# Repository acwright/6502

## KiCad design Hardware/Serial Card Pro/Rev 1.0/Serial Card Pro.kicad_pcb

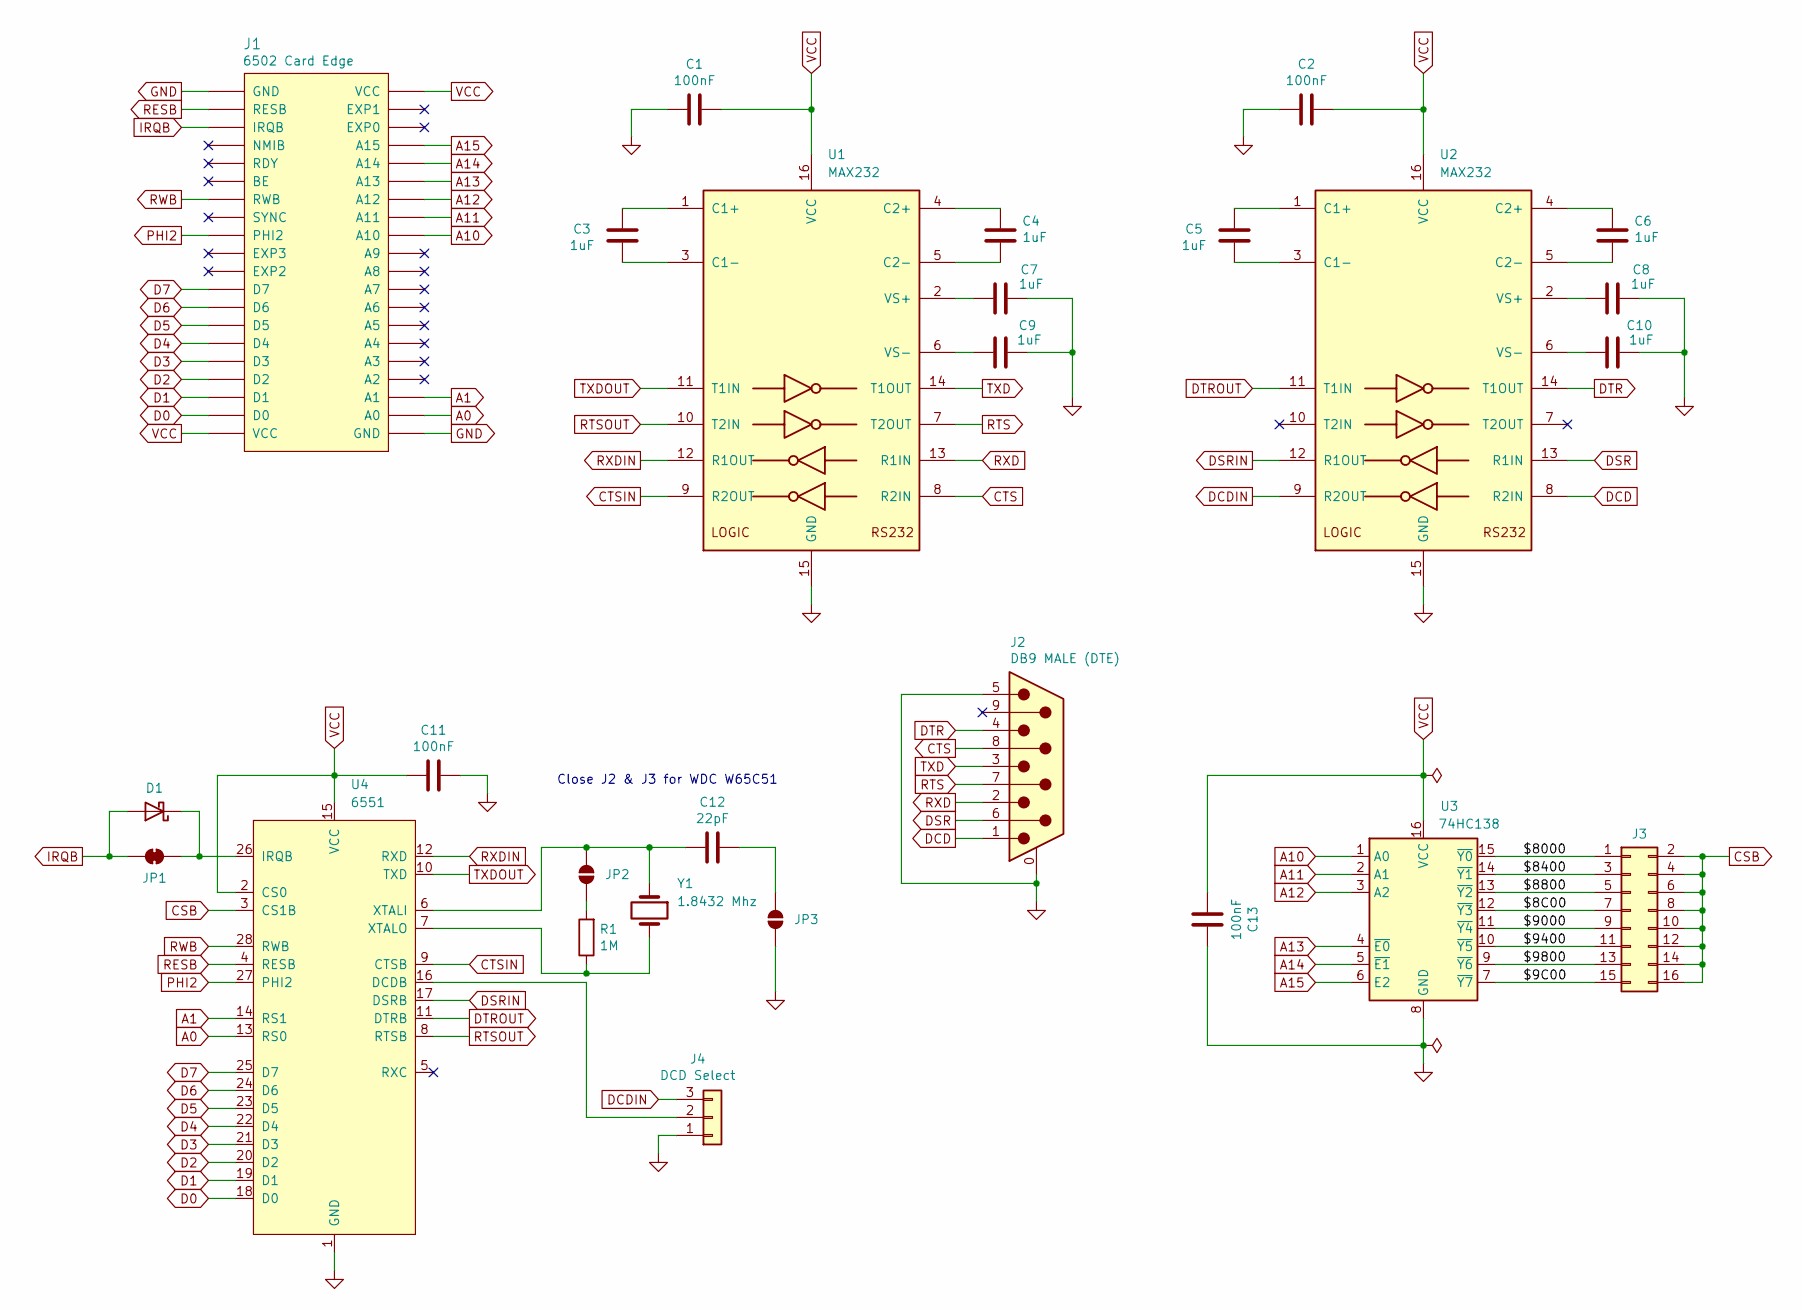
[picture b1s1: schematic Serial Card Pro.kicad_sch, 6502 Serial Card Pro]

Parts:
C1, C2, C11, C13: 100nF; C_0805_2012Metric; LCSC C49678
C3, C4, C5, C6, C7, C8, C9, C10: 1uF; C_0805_2012Metric; LCSC C28323
C12: 22pF; C_0805_2012Metric; LCSC C1804
D1: D_Schottky; D_DO-35_SOD27_P7.62mm_Horizontal
J1: 6502 Card Edge
J2: DB9 MALE (DTE); DSUB-9_Pins_Horizontal_P2.77x2.84mm_EdgePinOffset7.70mm_Hou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; MPN D09P33E4GX00LF; Digikey 609-1481-ND
J3: Conn_02x08_Odd_Even; PinHeader_2x08_P2.54mm_Vertical
J4: DCD Select; PinHeader_1x03_P2.54mm_Vertical
JP1: SolderJumper_2_Bridged; SolderJumper-2_P1.3mm_Bridged_RoundedPad1.0x1.5mm
JP2, JP3: SolderJumper_2_Open; SolderJumper-2_P1.3mm_Open_RoundedPad1.0x1.5mm
R1: 1M; R_0805_2012Metric; LCSC C103906
U1, U2: MAX232; MAX232D; LCSC C59824
U3: 74HC138; SOIC-16_3.9x9.9mm_P1.27mm; LCSC C5602
U4: 6551; DIP-28_W15.24mm_Socket_LongPads
Y1: 1.8432 Mhz; Crystal_HC49-U_Vertical

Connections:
/$8C00: J3.7, U3.12 (~Y3)
/$9C00: J3.15, U3.7 (~Y7)
/$8000: J3.1, U3.15 (~Y0)
/$8400: J3.3, U3.14 (~Y1)
/$8800: J3.5, U3.13 (~Y2)
/$9000: J3.9, U3.11 (~Y4)
/$9400: J3.11, U3.10 (~Y5)
/$9800: J3.13, U3.9 (~Y6)
A0: J1.A0, U4.13 (RS0)
A1: J1.A1, U4.14 (RS1)
A10: J1.A10, U3.1 (A0)
A11: J1.A11, U3.2 (A1)
A12: J1.A12, U3.3 (A2)
A13: J1.A13, U3.4 (~E0)
A14: J1.A14, U3.5 (~E1)
A15: J1.A15, U3.6 (E2)
CSB: J3.2, J3.4, J3.6, J3.8, J3.10, J3.12, J3.14, J3.16, U4.3 (CS1B)
CTS: J2.8, U1.8 (R2IN)
CTSIN: U1.9 (R2OUT), U4.9 (CTSB)
D0: J1.D0, U4.18 (D0)
D1: J1.D1, U4.19 (D1)
D2: J1.D2, U4.20 (D2)
D3: J1.D3, U4.21 (D3)
D4: J1.D4, U4.22 (D4)
D5: J1.D5, U4.23 (D5)
D6: J1.D6, U4.24 (D6)
D7: J1.D7, U4.25 (D7)
DCD: J2.1, U2.8 (R2IN)
DCDIN: J4.3, U2.9 (R2OUT)
DSR: J2.6, U2.13 (R1IN)
DSRIN: U2.12 (R1OUT), U4.17 (DSRB)
DTR: J2.4, U2.14 (T1OUT)
DTROUT: U2.11 (T1IN), U4.11 (DTRB)
GND: C1.1, C2.1, C7.2, C8.2, C9.2, C10.2, C11.2, C13.2, J1.GND, J2.0 (PAD), J2.5, J4.1, JP3.1 (A), U1.15 (GND), U2.15 (GND), U3.8 (GND), U4.1 (GND)
IRQB: D1.2 (A), J1.IRQB, JP1.1 (A)
unnamed: D1.1 (K), JP1.2 (B), U4.26 (IRQB)
unnamed: J4.2, U4.16 (DCDB)
unnamed: JP2.1 (A), R1.2
unnamed: C12.2, JP2.2 (B), U4.6 (XTALI), Y1.1
unnamed: C12.1, JP3.2 (B)
unnamed: C3.1, U1.1 (C1+)
unnamed: C3.2, U1.3 (C1-)
unnamed: C4.1, U1.4 (C2+)
unnamed: C4.2, U1.5 (C2-)
unnamed: C7.1, U1.2 (VS+)
unnamed: C9.1, U1.6 (VS-)
unnamed: C5.1, U2.1 (C1+)
unnamed: C5.2, U2.3 (C1-)
unnamed: C6.1, U2.4 (C2+)
unnamed: C6.2, U2.5 (C2-)
unnamed: C8.1, U2.2 (VS+)
unnamed: C10.1, U2.6 (VS-)
unnamed: R1.1, U4.7 (XTALO), Y1.2
PHI2: J1.PHI2, U4.27 (PHI2)
RESB: J1.RESB, U4.4 (RESB)
RTS: J2.7, U1.7 (T2OUT)
RTSOUT: U1.10 (T2IN), U4.8 (RTSB)
RWB: J1.RWB, U4.28 (RWB)
RXD: J2.2, U1.13 (R1IN)
RXDIN: U1.12 (R1OUT), U4.12 (RXD)
TXD: J2.3, U1.14 (T1OUT)
TXDOUT: U1.11 (T1IN), U4.10 (TXD)
VCC: C1.2, C2.2, C11.1, C13.1, J1.VCC, U1.16 (VCC), U2.16 (VCC), U3.16 (VCC), U4.2 (CS0), U4.15 (VCC)

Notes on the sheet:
Close J2 & J3 for WDC W65C51

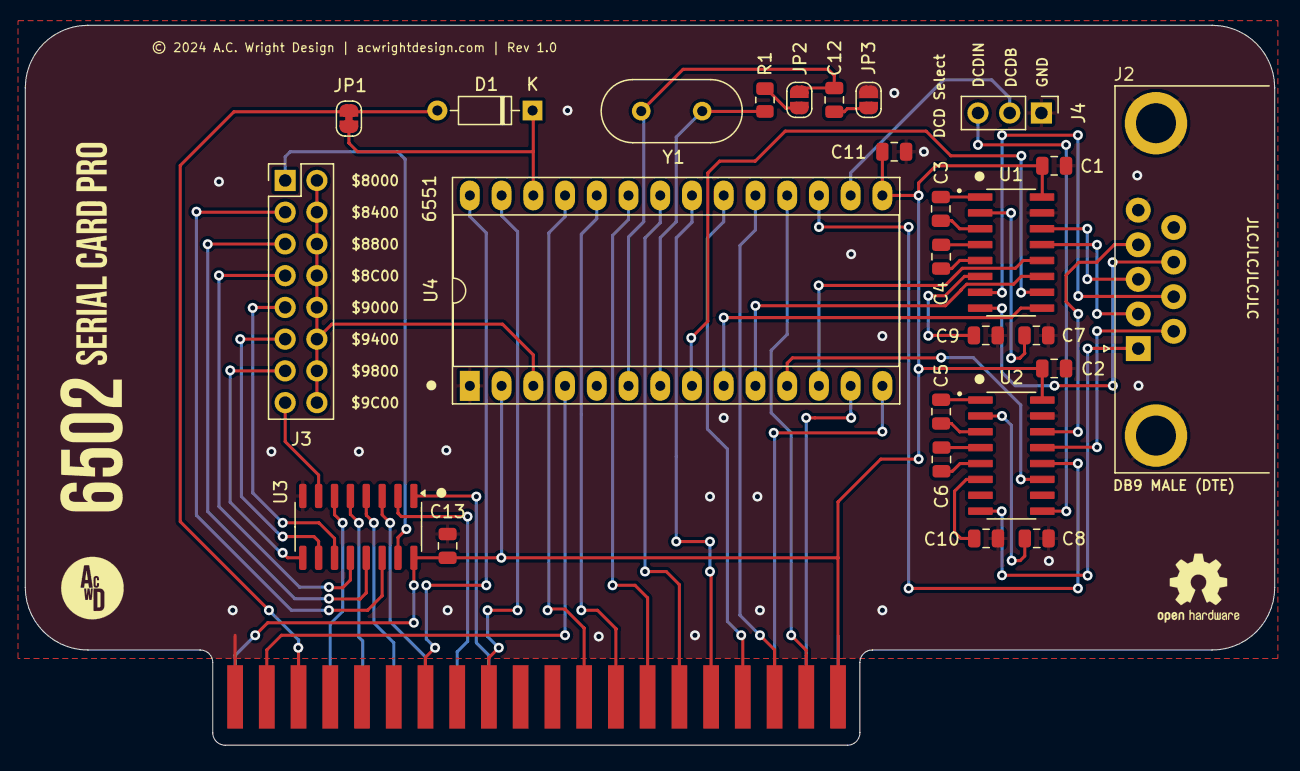
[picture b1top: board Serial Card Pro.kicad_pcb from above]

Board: 2 copper layers, 100.0 x 57.6 mm, 27 parts (0 on the bottom side), 63 nets.

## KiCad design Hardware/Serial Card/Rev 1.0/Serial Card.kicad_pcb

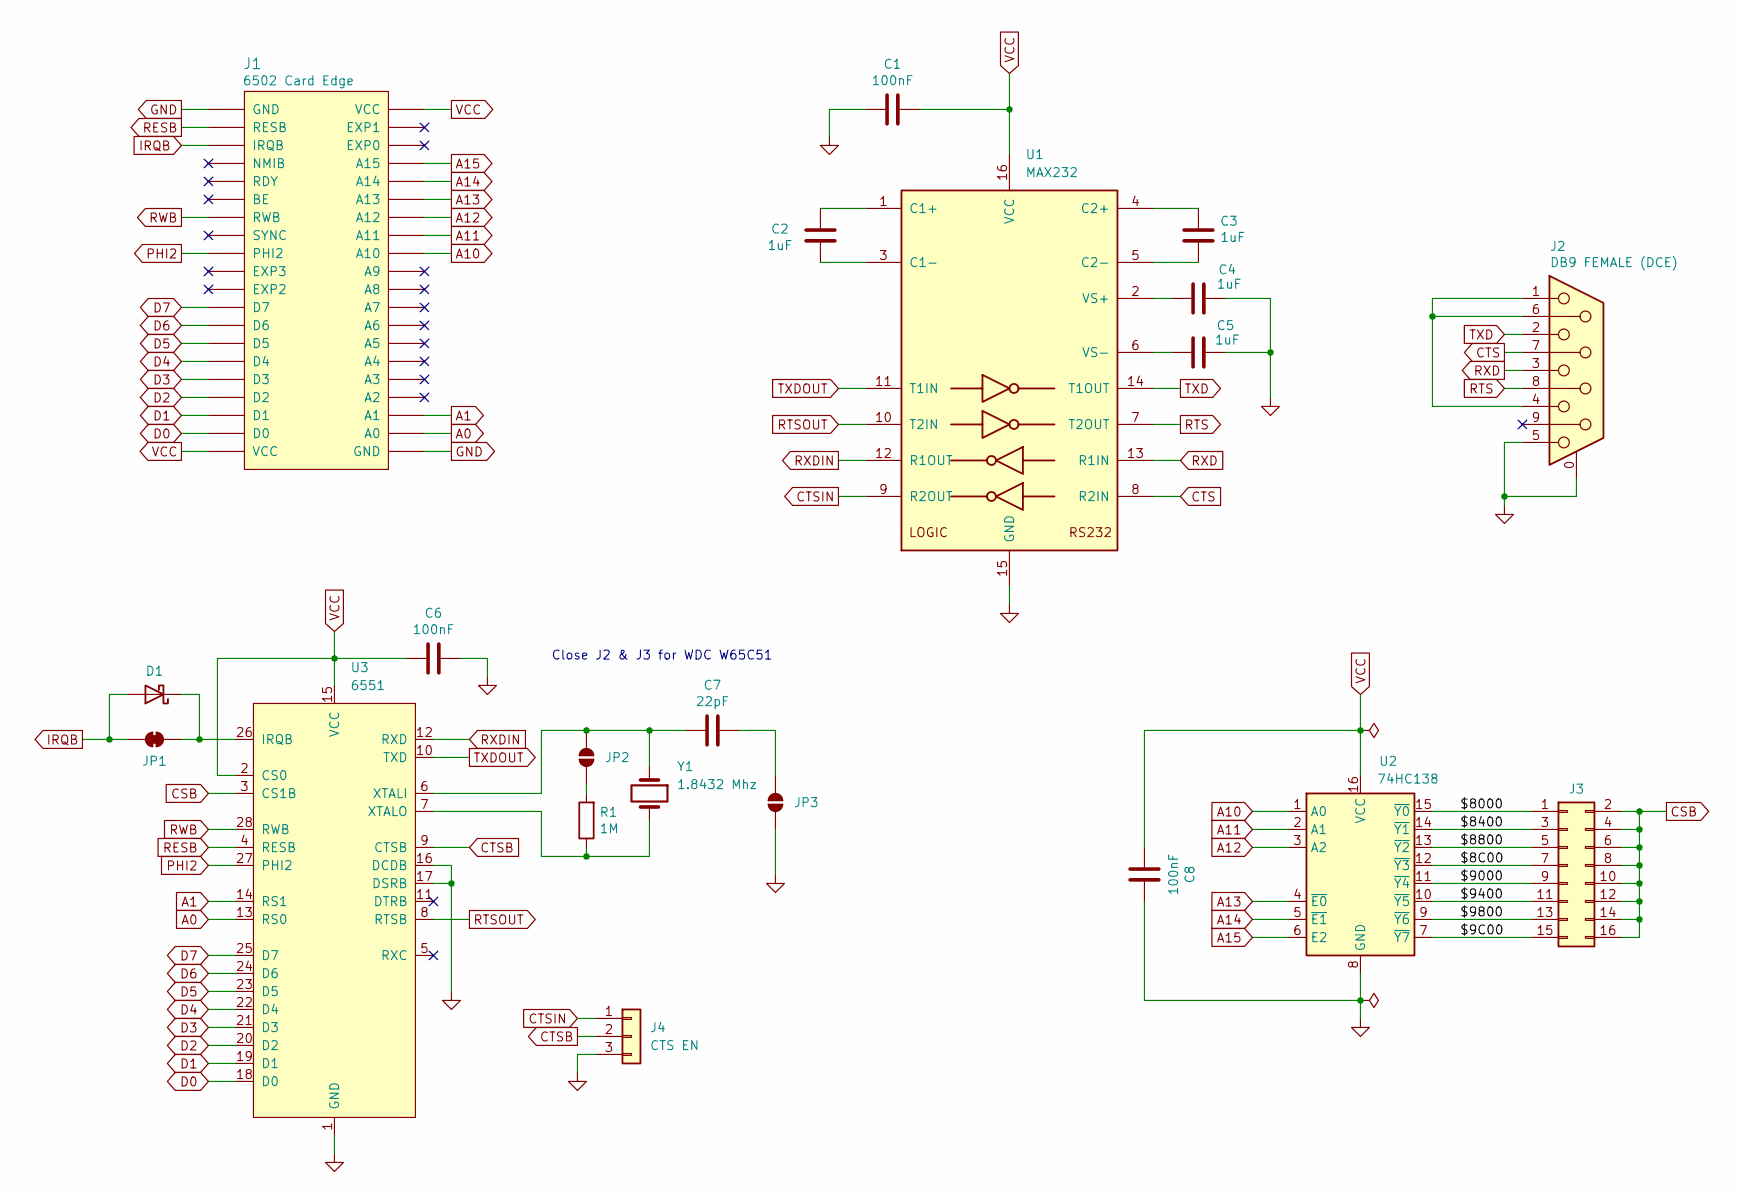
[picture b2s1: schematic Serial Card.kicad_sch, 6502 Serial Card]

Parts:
C1, C6, C8: 100nF; C_0805_2012Metric; LCSC C49678
C2, C3, C4, C5: 1uF; C_0805_2012Metric; LCSC C28323
C7: 22pF; C_0805_2012Metric; LCSC C1804
D1: D_Schottky; D_DO-35_SOD27_P7.62mm_Horizontal
J1: 6502 Card Edge
J2: DB9 FEMALE (DCE); DSUB-9_Socket_Horizontal_P2.77x2.84mm_EdgePinOffset7.70mm_H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; MPN D09S33E4GX00LF; Digikey 609-1487-ND
J3: Conn_02x08_Odd_Even; PinHeader_2x08_P2.54mm_Vertical
J4: CTS EN; PinHeader_1x03_P2.54mm_Vertical
JP1: SolderJumper_2_Bridged; SolderJumper-2_P1.3mm_Bridged_RoundedPad1.0x1.5mm
JP2, JP3: SolderJumper_2_Open; SolderJumper-2_P1.3mm_Open_RoundedPad1.0x1.5mm
R1: 1M; R_0805_2012Metric; LCSC C103906
U1: MAX232; MAX232D; LCSC C59824
U2: 74HC138; SOIC-16_3.9x9.9mm_P1.27mm; LCSC C5602
U3: 6551; DIP-28_W15.24mm_Socket_LongPads
Y1: 1.8432 Mhz; Crystal_HC49-U_Vertical

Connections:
/$8C00: J3.7, U2.12 (~Y3)
/$9C00: J3.15, U2.7 (~Y7)
/$8000: J3.1, U2.15 (~Y0)
/$8400: J3.3, U2.14 (~Y1)
/$8800: J3.5, U2.13 (~Y2)
/$9000: J3.9, U2.11 (~Y4)
/$9400: J3.11, U2.10 (~Y5)
/$9800: J3.13, U2.9 (~Y6)
A0: J1.A0, U3.13 (RS0)
A1: J1.A1, U3.14 (RS1)
A10: J1.A10, U2.1 (A0)
A11: J1.A11, U2.2 (A1)
A12: J1.A12, U2.3 (A2)
A13: J1.A13, U2.4 (~E0)
A14: J1.A14, U2.5 (~E1)
A15: J1.A15, U2.6 (E2)
CSB: J3.2, J3.4, J3.6, J3.8, J3.10, J3.12, J3.14, J3.16, U3.3 (CS1B)
CTS: J2.7, U1.8 (R2IN)
CTSB: J4.2, U3.9 (CTSB)
CTSIN: J4.1, U1.9 (R2OUT)
D0: J1.D0, U3.18 (D0)
D1: J1.D1, U3.19 (D1)
D2: J1.D2, U3.20 (D2)
D3: J1.D3, U3.21 (D3)
D4: J1.D4, U3.22 (D4)
D5: J1.D5, U3.23 (D5)
D6: J1.D6, U3.24 (D6)
D7: J1.D7, U3.25 (D7)
GND: C1.1, C4.2, C5.2, C6.2, C8.2, J1.GND, J2.0 (PAD), J2.5, J4.3, JP3.1 (A), U1.15 (GND), U2.8 (GND), U3.1 (GND), U3.16 (DCDB), U3.17 (DSRB)
IRQB: D1.2 (A), J1.IRQB, JP1.1 (A)
unnamed: D1.1 (K), JP1.2 (B), U3.26 (IRQB)
unnamed: J2.1, J2.4, J2.6
unnamed: JP2.1 (A), R1.2
unnamed: C7.2, JP2.2 (B), U3.6 (XTALI), Y1.1
unnamed: C7.1, JP3.2 (B)
unnamed: C2.1, U1.1 (C1+)
unnamed: C2.2, U1.3 (C1-)
unnamed: C3.1, U1.4 (C2+)
unnamed: C3.2, U1.5 (C2-)
unnamed: C4.1, U1.2 (VS+)
unnamed: C5.1, U1.6 (VS-)
unnamed: R1.1, U3.7 (XTALO), Y1.2
PHI2: J1.PHI2, U3.27 (PHI2)
RESB: J1.RESB, U3.4 (RESB)
RTS: J2.8, U1.7 (T2OUT)
RTSOUT: U1.10 (T2IN), U3.8 (RTSB)
RWB: J1.RWB, U3.28 (RWB)
RXD: J2.3, U1.13 (R1IN)
RXDIN: U1.12 (R1OUT), U3.12 (RXD)
TXD: J2.2, U1.14 (T1OUT)
TXDOUT: U1.11 (T1IN), U3.10 (TXD)
VCC: C1.2, C6.1, C8.1, J1.VCC, U1.16 (VCC), U2.16 (VCC), U3.2 (CS0), U3.15 (VCC)

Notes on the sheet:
Close J2 & J3 for WDC W65C51

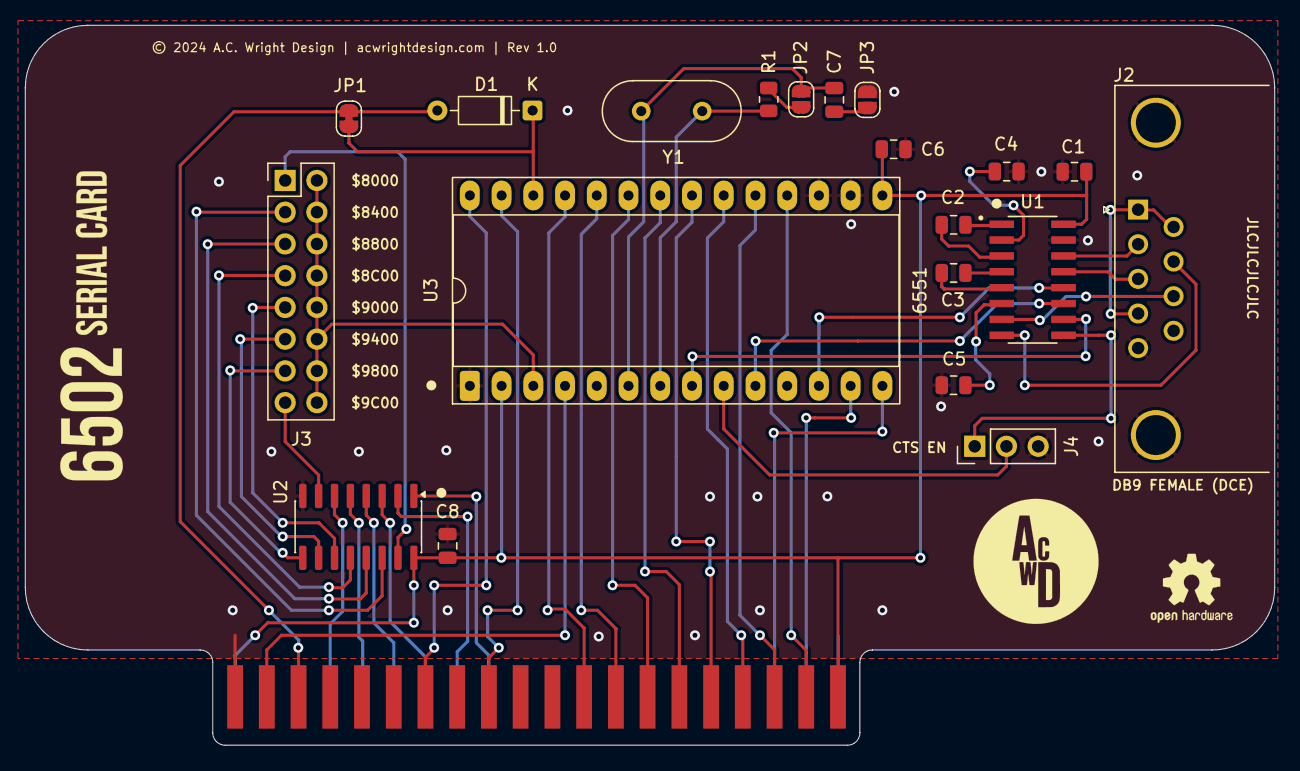
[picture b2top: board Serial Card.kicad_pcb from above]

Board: 2 copper layers, 100.0 x 57.6 mm, 21 parts (0 on the bottom side), 52 nets.

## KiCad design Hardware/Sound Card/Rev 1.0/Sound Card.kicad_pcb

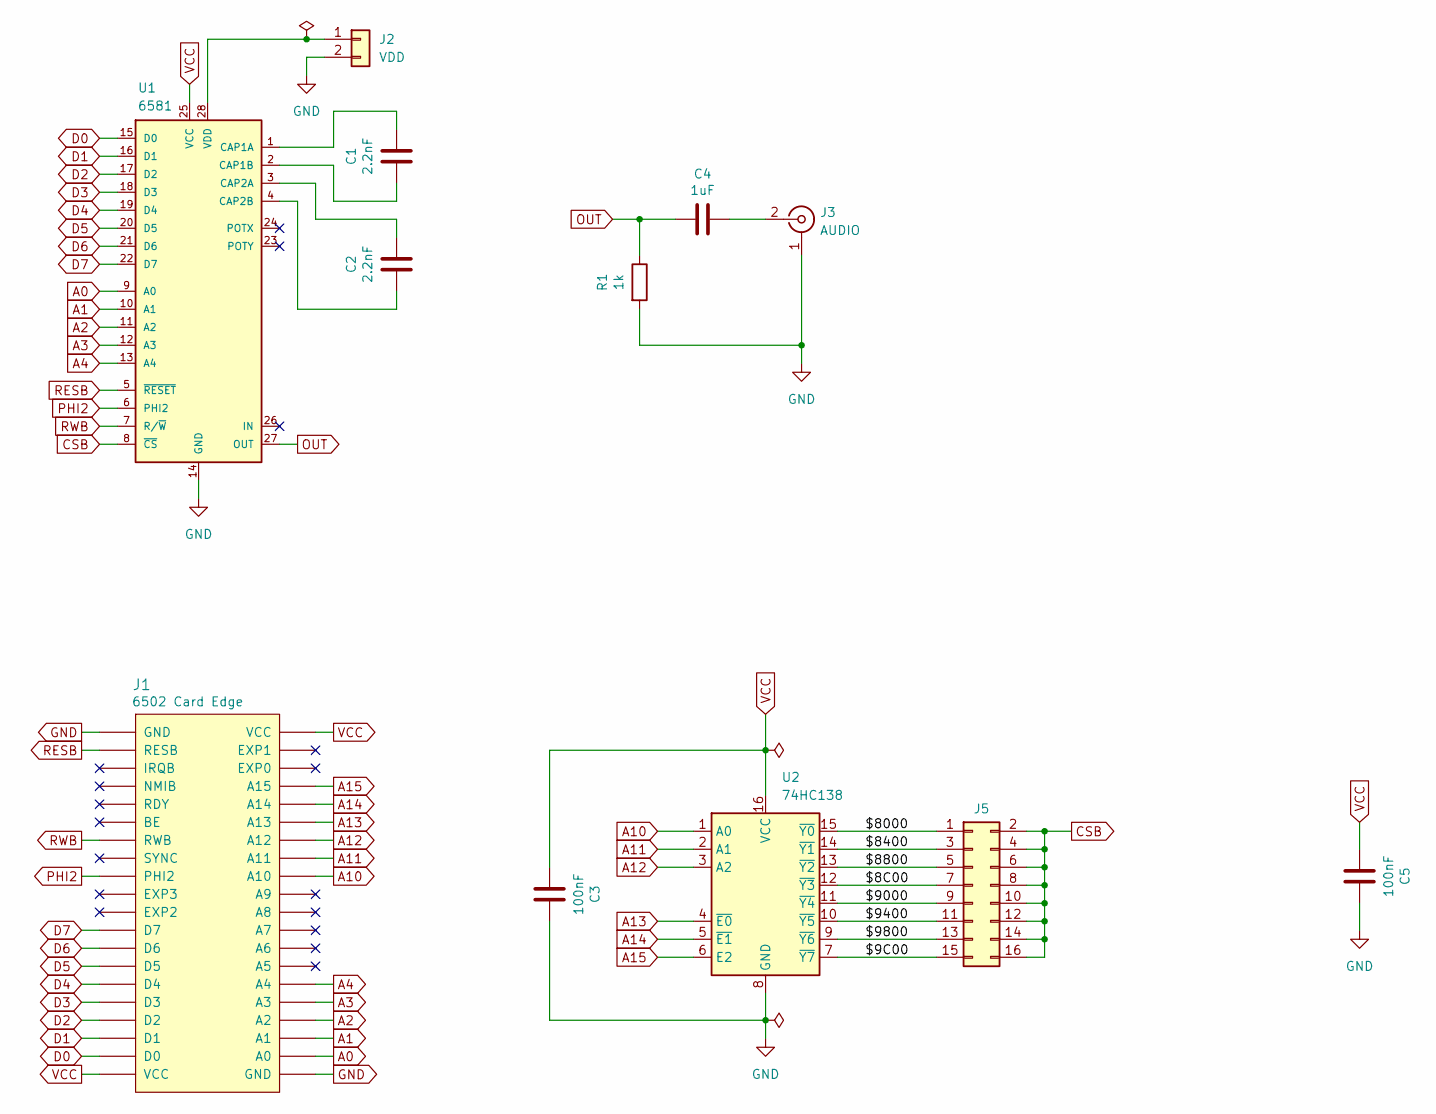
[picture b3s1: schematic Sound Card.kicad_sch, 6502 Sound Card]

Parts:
C1, C2: 2.2nF; C_0805_2012Metric; LCSC C28260
C3, C5: 100nF; C_0805_2012Metric; LCSC C49678
C4: 1uF; C_0805_2012Metric; LCSC C28323
J1: 6502 Card Edge
J2: VDD; JST_XH_B2B-XH-A_1x02_P2.50mm_Vertical
J3: AUDIO; SWITCHCRAFT_PJRAN1X1U02X
J5: Conn_02x08_Odd_Even; PinHeader_2x08_P2.54mm_Vertical
R1: 1k; R_0805_2012Metric; LCSC C17513
U1: 6581; DIP-28_W15.24mm_Socket_LongPads
U2: 74HC138; SOIC-16_3.9x9.9mm_P1.27mm; LCSC C5602

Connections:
/$8C00: J5.7, U2.12 (~Y3)
/$9C00: J5.15, U2.7 (~Y7)
/$8000: J5.1, U2.15 (~Y0)
/$8400: J5.3, U2.14 (~Y1)
/$8800: J5.5, U2.13 (~Y2)
/$9000: J5.9, U2.11 (~Y4)
/$9400: J5.11, U2.10 (~Y5)
/$9800: J5.13, U2.9 (~Y6)
A0: J1.A0, U1.9 (A0)
A1: J1.A1, U1.10 (A1)
A2: J1.A2, U1.11 (A2)
A3: J1.A3, U1.12 (A3)
A4: J1.A4, U1.13 (A4)
A10: J1.A10, U2.1 (A0)
A11: J1.A11, U2.2 (A1)
A12: J1.A12, U2.3 (A2)
A13: J1.A13, U2.4 (~E0)
A14: J1.A14, U2.5 (~E1)
A15: J1.A15, U2.6 (E2)
CSB: J5.2, J5.4, J5.6, J5.8, J5.10, J5.12, J5.14, J5.16, U1.8 (~CS)
D0: J1.D0, U1.15 (D0)
D1: J1.D1, U1.16 (D1)
D2: J1.D2, U1.17 (D2)
D3: J1.D3, U1.18 (D3)
D4: J1.D4, U1.19 (D4)
D5: J1.D5, U1.20 (D5)
D6: J1.D6, U1.21 (D6)
D7: J1.D7, U1.22 (D7)
GND: C3.2, C5.2, J1.GND, J2.2, J3.1 (Ext), R1.2, U1.14 (GND), U2.8 (GND)
unnamed: J2.1, U1.28 (VDD)
unnamed: C4.2, J3.2 (In)
unnamed: C1.2, U1.1 (CAP1A)
unnamed: C1.1, U1.2 (CAP1B)
unnamed: C2.2, U1.3 (CAP2A)
unnamed: C2.1, U1.4 (CAP2B)
OUT: C4.1, R1.1, U1.27 (OUT)
PHI2: J1.PHI2, U1.6 (PHI2)
RESB: J1.RESB, U1.5 (~RESET)
RWB: J1.RWB, U1.7 (R/~W)
VCC: C3.1, C5.1, J1.VCC, U1.25 (VCC), U2.16 (VCC)

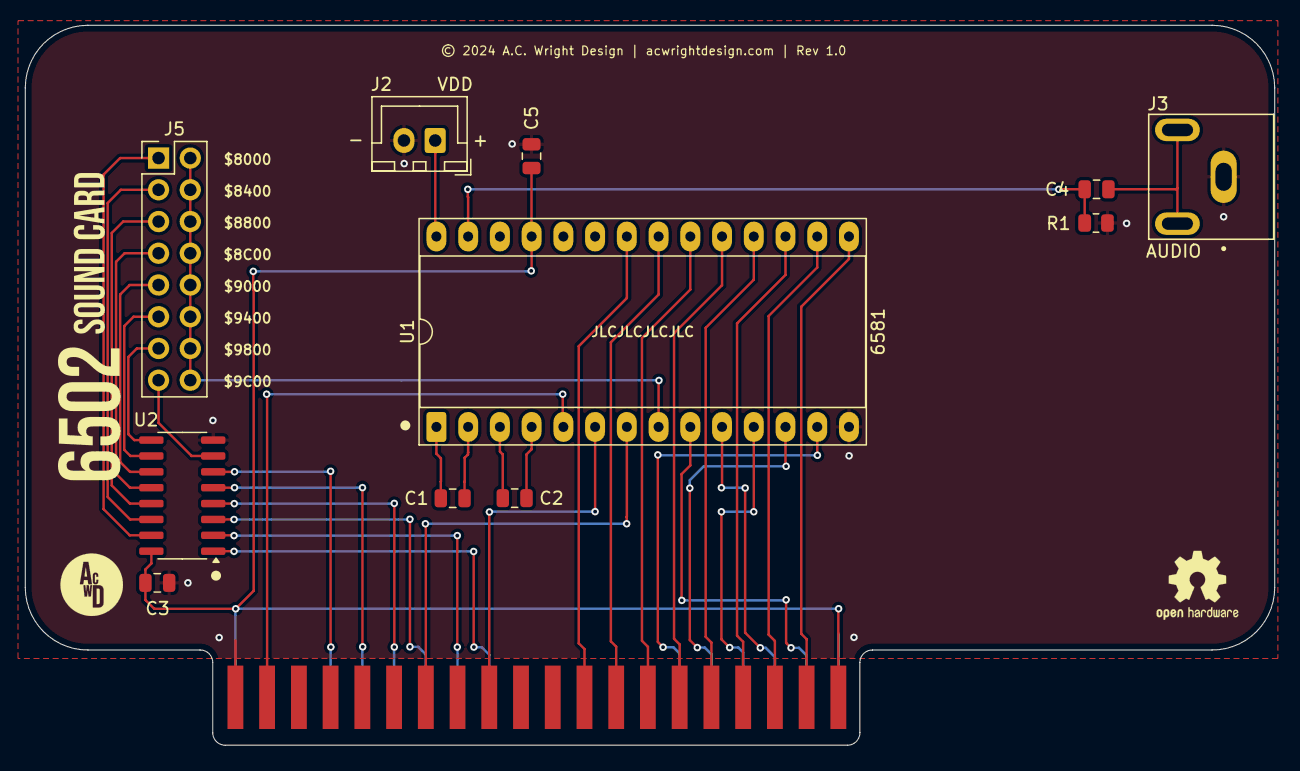
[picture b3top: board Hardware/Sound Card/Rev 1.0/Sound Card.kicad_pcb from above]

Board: 2 copper layers, 100.0 x 57.6 mm, 12 parts (0 on the bottom side), 40 nets.

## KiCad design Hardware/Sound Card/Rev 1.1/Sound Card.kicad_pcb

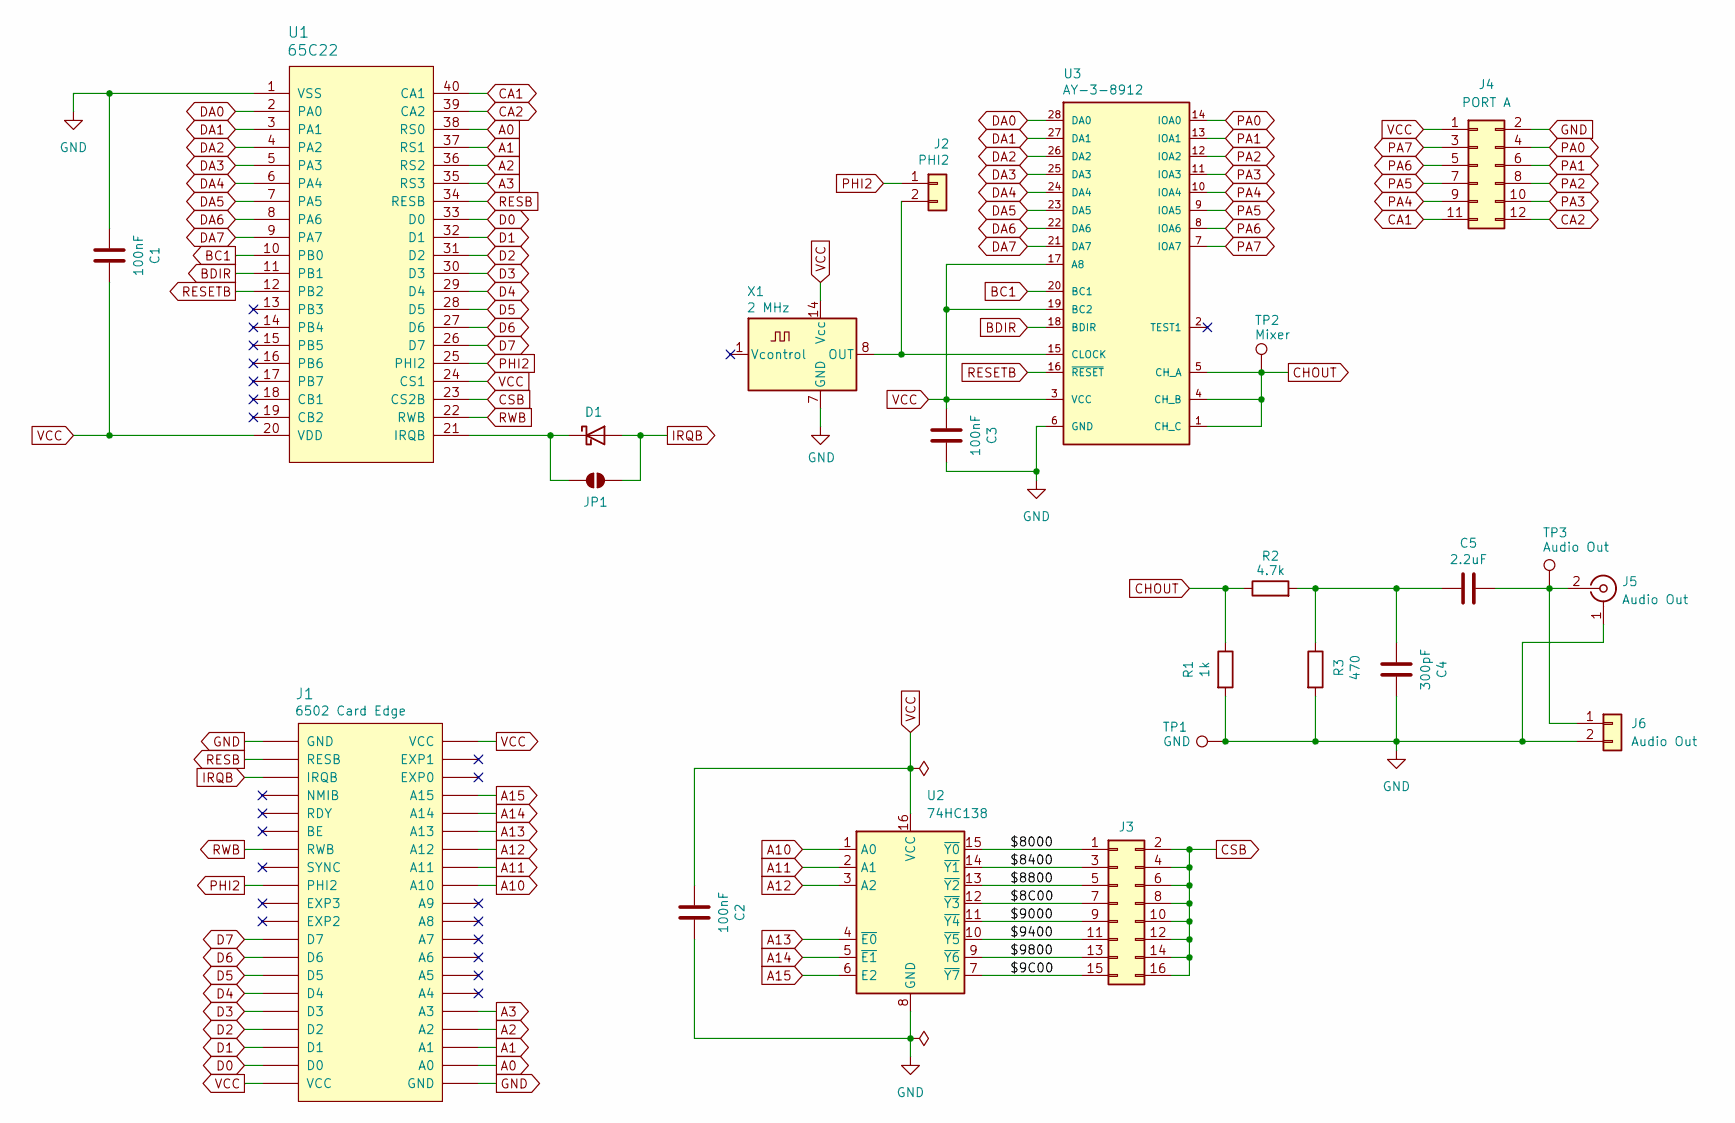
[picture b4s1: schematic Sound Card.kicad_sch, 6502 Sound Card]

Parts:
C1, C2, C3: 100nF; C_0805_2012Metric; LCSC C49678
C4: 300pF; C_0805_2012Metric; LCSC C37635
C5: 2.2uF; C_0805_2012Metric; LCSC C377773
D1: D_Schottky; D_DO-35_SOD27_P7.62mm_Horizontal
J1: 6502 Card Edge
J2: PHI2; PinHeader_1x02_P2.54mm_Vertical
J3: Conn_02x08_Odd_Even; PinHeader_2x08_P2.54mm_Vertical
J4: PORT A; PinHeader_2x06_P2.54mm_Vertical
J5: Audio Out; SWITCHCRAFT_PJRAN1X1U02X
J6: Audio Out; JST_XH_B2B-XH-A_1x02_P2.50mm_Vertical
JP1: SolderJumper_2_Bridged; SolderJumper-2_P1.3mm_Open_RoundedPad1.0x1.5mm
R1: 1k; R_0805_2012Metric; LCSC C17513
R2: 4.7k; R_0805_2012Metric; LCSC C17673
R3: 470; R_0805_2012Metric; LCSC C17710
TP1: GND; TestPoint_Pad_1.5x1.5mm
TP2: Mixer; TestPoint_Pad_1.5x1.5mm
TP3: Audio Out; TestPoint_Pad_1.5x1.5mm
U1: 65C22; DIP-40_W15.24mm_Socket_LongPads
U2: 74HC138; SOIC-16_3.9x9.9mm_P1.27mm; LCSC C5602
U3: AY-3-8912; DIP-28_W15.24mm_Socket_LongPads
X1: 2 MHz; Oscillator_DIP-14

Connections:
/$8C00: J3.7, U2.12 (~Y3)
/$9C00: J3.15, U2.7 (~Y7)
/$8000: J3.1, U2.15 (~Y0)
/$8400: J3.3, U2.14 (~Y1)
/$8800: J3.5, U2.13 (~Y2)
/$9000: J3.9, U2.11 (~Y4)
/$9400: J3.11, U2.10 (~Y5)
/$9800: J3.13, U2.9 (~Y6)
A0: J1.A0, U1.38 (RS0)
A1: J1.A1, U1.37 (RS1)
A2: J1.A2, U1.36 (RS2)
A3: J1.A3, U1.35 (RS3)
A10: J1.A10, U2.1 (A0)
A11: J1.A11, U2.2 (A1)
A12: J1.A12, U2.3 (A2)
A13: J1.A13, U2.4 (~E0)
A14: J1.A14, U2.5 (~E1)
A15: J1.A15, U2.6 (E2)
BC1: U1.10 (PB0), U3.20 (BC1)
BDIR: U1.11 (PB1), U3.18 (BDIR)
CA1: J4.11, U1.40 (CA1)
CA2: J4.12, U1.39 (CA2)
CHOUT: R1.1, R2.1, TP2.1, U3.1 (CH_C), U3.4 (CH_B), U3.5 (CH_A)
CSB: J3.2, J3.4, J3.6, J3.8, J3.10, J3.12, J3.14, J3.16, U1.23 (CS2B)
D0: J1.D0, U1.33 (D0)
D1: J1.D1, U1.32 (D1)
D2: J1.D2, U1.31 (D2)
D3: J1.D3, U1.30 (D3)
D4: J1.D4, U1.29 (D4)
D5: J1.D5, U1.28 (D5)
D6: J1.D6, U1.27 (D6)
D7: J1.D7, U1.26 (D7)
DA0: U1.2 (PA0), U3.28 (DA0)
DA1: U1.3 (PA1), U3.27 (DA1)
DA2: U1.4 (PA2), U3.26 (DA2)
DA3: U1.5 (PA3), U3.25 (DA3)
DA4: U1.6 (PA4), U3.24 (DA4)
DA5: U1.7 (PA5), U3.23 (DA5)
DA6: U1.8 (PA6), U3.22 (DA6)
DA7: U1.9 (PA7), U3.21 (DA7)
GND: C1.1, C2.2, C3.2, C4.2, J1.GND, J4.2, J5.1 (Ext), J6.2, R1.2, R3.2, TP1.1, U1.1 (VSS), U2.8 (GND), U3.6 (GND), X1.7 (GND)
IRQB: D1.2 (A), J1.IRQB, JP1.2 (B)
unnamed: C4.1, C5.1, R2.2, R3.1
unnamed: D1.1 (K), JP1.1 (A), U1.21 (IRQB)
unnamed: J2.2, U3.15 (CLOCK), X1.8 (OUT)
unnamed: C5.2, J5.2 (In), J6.1, TP3.1
PA0: J4.4, U3.14 (IOA0)
PA1: J4.6, U3.13 (IOA1)
PA2: J4.8, U3.12 (IOA2)
PA3: J4.10, U3.11 (IOA3)
PA4: J4.9, U3.10 (IOA4)
PA5: J4.7, U3.9 (IOA5)
PA6: J4.5, U3.8 (IOA6)
PA7: J4.3, U3.7 (IOA7)
PHI2: J1.PHI2, J2.1, U1.25 (PHI2)
RESB: J1.RESB, U1.34 (RESB)
RESETB: U1.12 (PB2), U3.16 (~RESET)
RWB: J1.RWB, U1.22 (RWB)
VCC: C1.2, C2.1, C3.1, J1.VCC, J4.1, U1.20 (VDD), U1.24 (CS1), U2.16 (VCC), U3.3 (VCC), U3.17 (A8), U3.19 (BC2), X1.14 (Vcc)

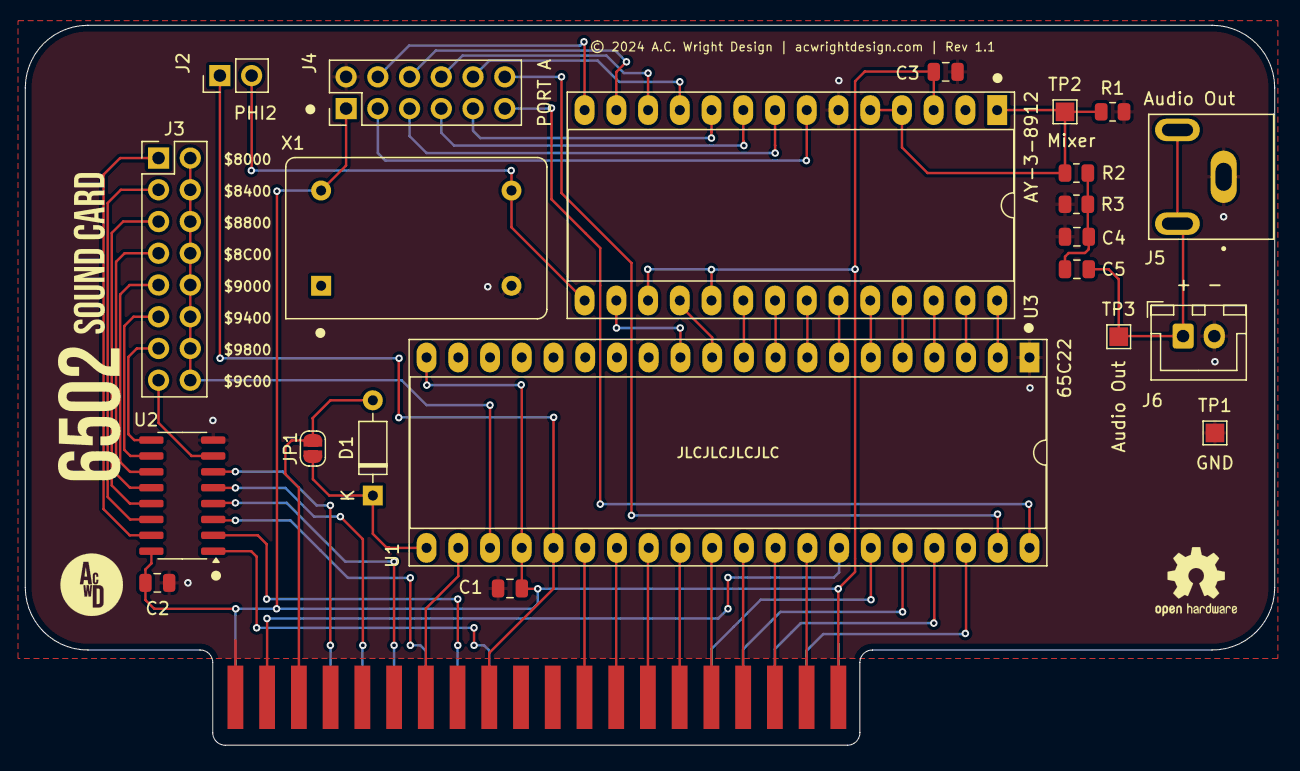
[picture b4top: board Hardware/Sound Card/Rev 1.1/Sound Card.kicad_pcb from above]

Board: 2 copper layers, 100.0 x 57.6 mm, 23 parts (0 on the bottom side), 59 nets.

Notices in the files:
Hardware/Serial Card Pro/Rev 1.0/Serial Card Pro.kicad_pcb:
© 2024 A.C. Wright Design | acwrightdesign.com | Rev 1.0
Hardware/Sound Card/Rev 1.1/Sound Card.kicad_pcb:
© 2024 A.C. Wright Design | acwrightdesign.com | Rev 1.1
